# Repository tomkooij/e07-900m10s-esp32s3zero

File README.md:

# e07-900m10s adapter board for esp32s3 zero
Adapter board for [ebyte e07-900m10s CC1101 module](https://www.ebyte.com/en/product-view-news.html?id=1567) and [ESP32-s3-zero](https://www.waveshare.com/wiki/ESP32-S3-Zero)

TODO:
 - Use esp32-s3-zero Kicad module (in this folder) instead of two connectors

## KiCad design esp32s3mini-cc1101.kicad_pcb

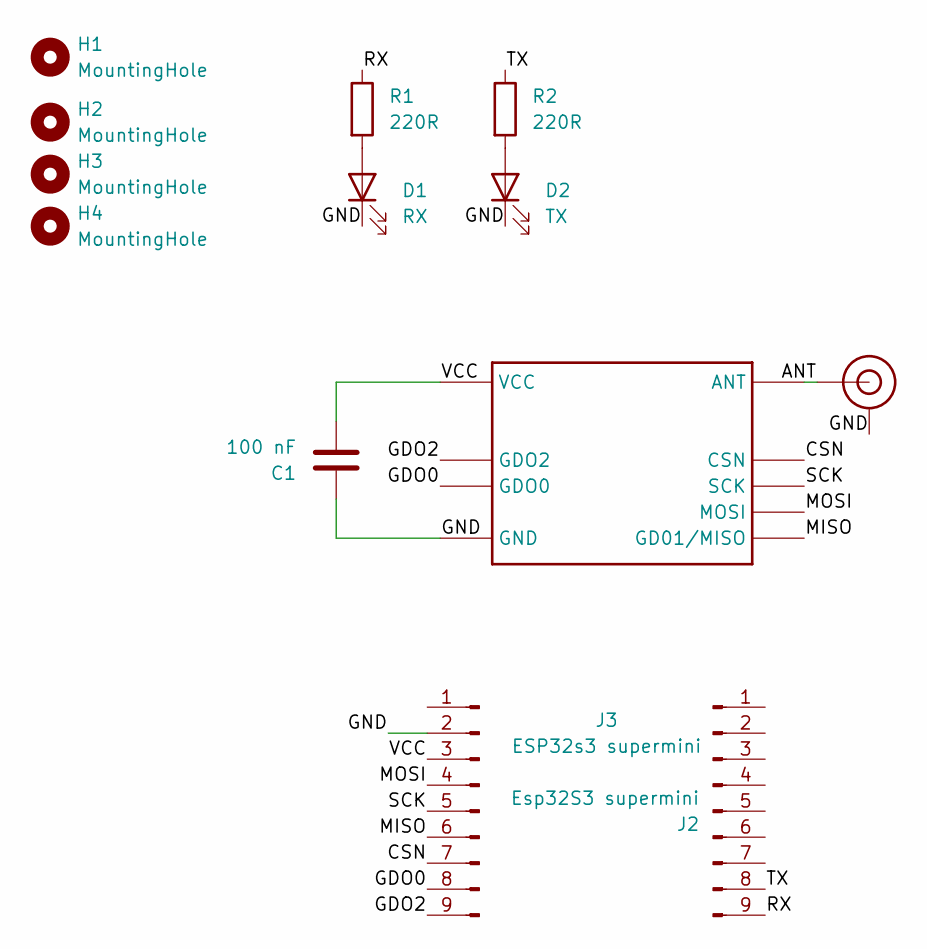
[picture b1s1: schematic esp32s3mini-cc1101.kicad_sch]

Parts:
1: E07-900M10S
C1: 100 nF; C_1206_3216Metric_Pad1.33x1.80mm_HandSolder
D1: RX; LED_1206_3216Metric_Pad1.42x1.75mm_HandSolder
D2: TX; LED_1206_3216Metric_Pad1.42x1.75mm_HandSolder
H1, H2, H3, H4: MountingHole; MountingHole_3.2mm_M3
J2: Esp32S3 supermini; PinSocket_1x09_P2.54mm_Vertical
J3: ESP32s3 supermini; PinSocket_1x09_P2.54mm_Vertical
J$1: SMA_PAD
R1, R2: 220R; R_1206_3216Metric_Pad1.30x1.75mm_HandSolder

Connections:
/ANT: 1.21 (ANT), J$1.ANT0 (ANT), J$1.ANT1 (ANT), J$1.ANT2 (ANT)
/CSN: 1.19 (CSN), J3.7
/GDO0: 1.15 (GDO0), J3.8
/GDO2: 1.14 (GDO2), J3.9
/GND: 1.1 (GND), 1.2 (GND), 1.3 (GND), 1.4 (GND), 1.5 (GND), 1.11 (GND), 1.12 (GND), 1.20 (GND), 1.22 (GND), C1.1, D1.1 (K), D2.1 (K), J3.2, J$1.GND3 (GND), J$1.GND4 (GND), J$1.GND5 (GND), J$1.GND6 (GND)
/MISO: 1.16 (GD01/MISO), J3.6
/MOSI: 1.17 (MOSI), J3.4
/RX: J2.9, R1.1
/SCK: 1.18 (SCK), J3.5
/TX: J2.8, R2.1
/VCC: 1.9 (VCC), C1.2, J3.3
unnamed: D1.2 (A), R1.2
unnamed: D2.2 (A), R2.2

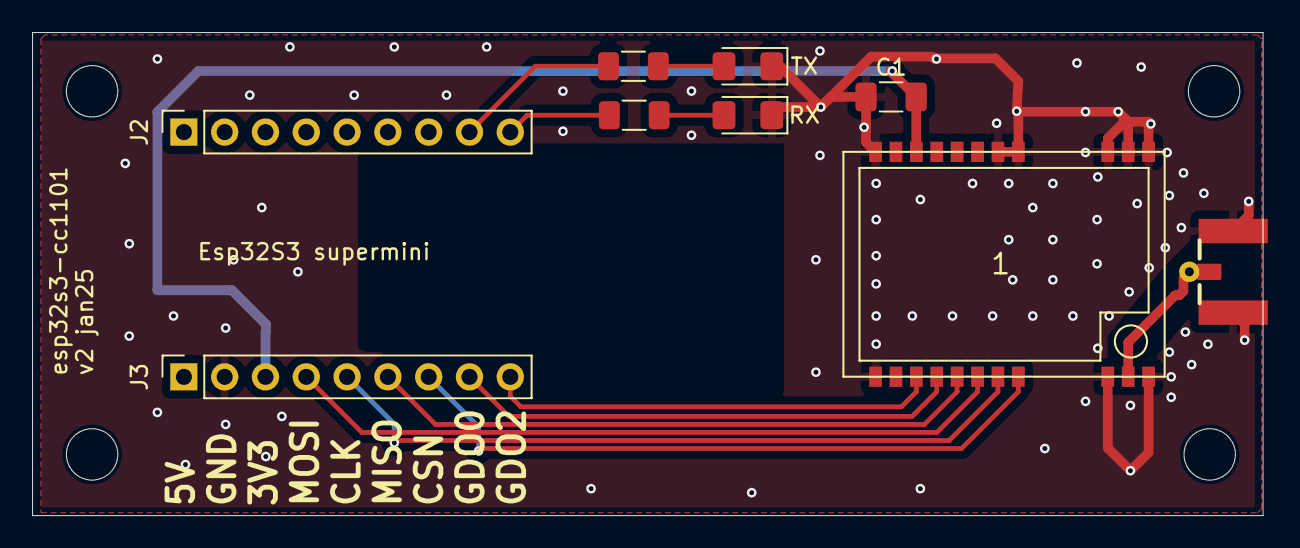
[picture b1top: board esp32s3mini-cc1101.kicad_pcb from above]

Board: 2 copper layers, 76.6 x 30.1 mm, 13 parts (0 on the bottom side), 13 nets.

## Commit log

2025-01-15 Kicad files
2025-01-15 Add pics
2025-01-16 ESP32-s3-zero instead of supermini
    The board is called "zero" instead of supermini
